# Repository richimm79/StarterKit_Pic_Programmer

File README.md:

# StarterKit_Pic_Programmer
PIC Microcontroller programmer using the StartKit

Please refer to the PIC In-Circuit programming document to understand the meaning of the following content.

This project is not intended to be a professional tool.
There are many programmers on the market and is senseless to create another one.
Use this as a didactic project to understand how the In-Circuit programming works.

This project is a full In-Circuit PIC10 programmer using the StartKit as cpu for logic signal generation.
You need the Adapter circuit to connect the StarteKit to the PIC10 cpu.
This adapter will work in two different ways.
- the socket can be use to insert the PIC device that needs programming. This is clearly a "non In-Circuit" option.
- in the socket can be inserted a plug that connect to the target board. This is the In-Circuit option.
I'm planning to create a 3D printer plug for rapid attach on the target board.
This plug will get the signals from the socket.

You may create your own branch.
You may create your own fork but following the license.
Up to now there is no restriction in wath can be changed.
I just ask to not introduce modern programming paradigmas.
Keep code simple so that anyon can read and understand.

Create a pull-request if you wish to merge it into main.

See wiki page for detailed explanation.
	https://github.com/richimm79/StarterKit_Pic_Programmer/wiki

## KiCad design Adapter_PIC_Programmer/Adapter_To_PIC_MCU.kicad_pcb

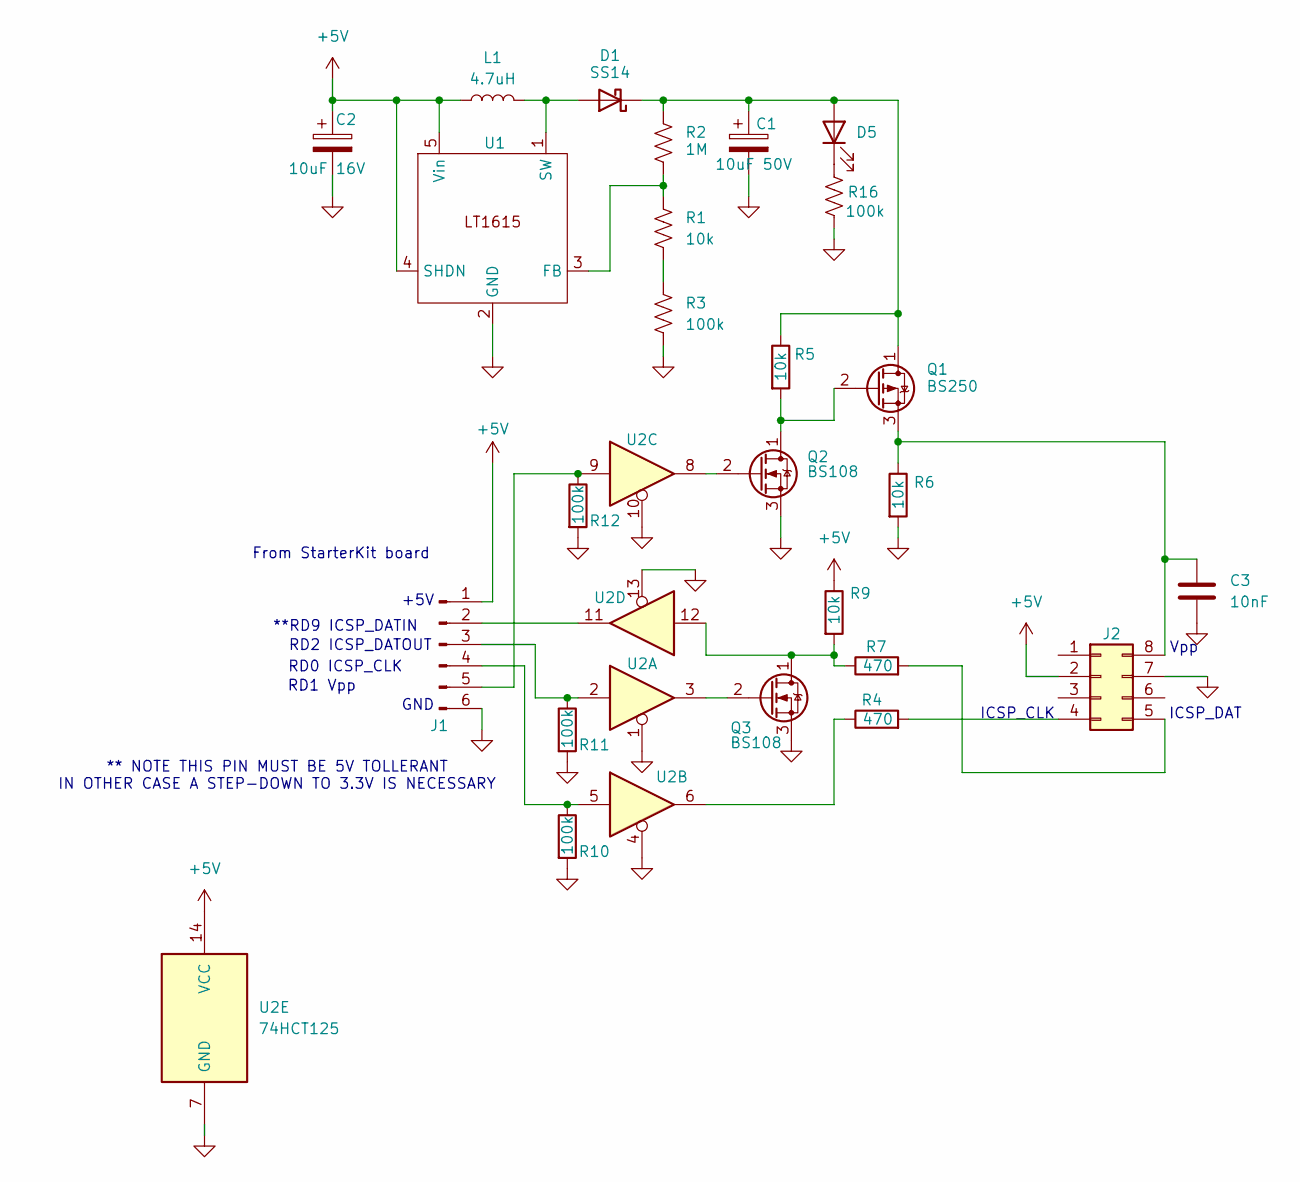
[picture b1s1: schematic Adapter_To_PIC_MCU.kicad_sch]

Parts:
C1: 10uF 50V; CP_Elec_6.3x7.7
C2: 10uF 16V; CP_Elec_5x5.4
C3: 10nF; C_0805_2012Metric_Pad1.18x1.45mm_HandSolder
D1: SS14; D_SMA_Handsoldering
D5: LED; LED_0603_1608Metric
J1: Conn_01x06_Pin; PinSocket_1x06_P2.54mm_SMD
J2: Conn_02x04_Counter_Clockwise; Socket DIL-8 wide pins SMD
L1: 4.7uH; L_Bourns-SRU8028_8.0x8.0mm
Q1: BS250; TO-92L_Inline_Wide SMD_facedown
Q2, Q3: BS108; TO-92L_Inline_Wide SMD_faceup
R1, R5, R6, R9: 10k; R_0805_2012Metric_Pad1.20x1.40mm_HandSolder
R2: 1M; R_0805_2012Metric_Pad1.20x1.40mm_HandSolder
R3, R10, R11, R12, R16: 100k; R_0805_2012Metric_Pad1.20x1.40mm_HandSolder
R4, R7: 470; R_0805_2012Metric_Pad1.20x1.40mm_HandSolder
U1: LT1615; SOT-23-5
U2: 74HCT125; SOIC-14_3.9x8.7mm_P1.27mm

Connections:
+5V: C2.1, J1.1, J2.2, L1.1, R9.1, U1.4 (SHDN), U1.5 (Vin), U2.14 (VCC)
GND: C1.2, C2.2, C3.2, J1.6, J2.7, Q2.3 (S), Q3.3 (S), R3.2, R6.2, R10.2, R11.2, R12.2, R16.2, U1.2 (GND), U2.1, U2.4, U2.7 (GND), U2.10, U2.13
unnamed: D1.2 (A), L1.2, U1.1 (SW)
unnamed: C1.1, D1.1 (K), D5.2 (A), Q1.1 (D), R2.1, R5.1
unnamed: D5.1 (K), R16.1
unnamed: J1.2, U2.11
unnamed: J1.3, R11.1, U2.2
unnamed: J1.4, R10.1, U2.5
unnamed: J1.5, R12.1, U2.9
unnamed: J2.4, R4.2
unnamed: J2.5, R7.2
unnamed: C3.1, J2.8, Q1.3 (S), R6.1
unnamed: Q1.2 (G), Q2.1 (D), R5.2
unnamed: Q2.2 (G), U2.8
unnamed: Q3.1 (D), R7.1, R9.2, U2.12
unnamed: Q3.2 (G), U2.3
unnamed: R1.2, R3.1
unnamed: R4.1, U2.6
unnamed: R1.1, R2.2, U1.3 (FB)

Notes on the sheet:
RD2 ICSP_DATOUT
+5V
RD0 ICSP_CLK
RD1 Vpp
From StarterKit board
ICSP_CLK
**RD9 ICSP_DATIN
** NOTE THIS PIN MUST BE 5V TOLLERANT IN OTHER CASE A STEP-DOWN TO 3.3V IS NECESSARY
ICSP_DAT
Vpp
GND

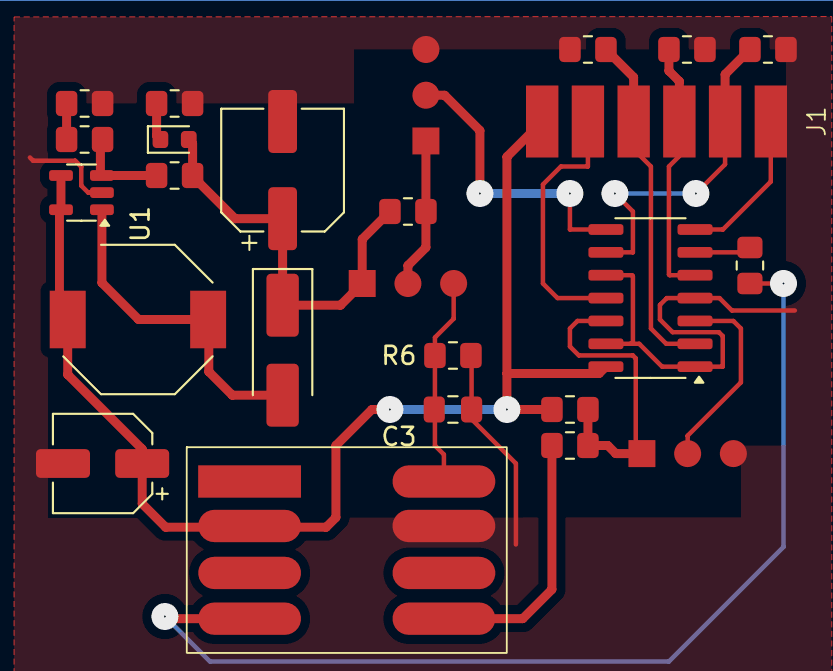
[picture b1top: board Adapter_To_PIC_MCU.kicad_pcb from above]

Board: 2 copper layers, 25 parts (0 on the bottom side), 19 nets.

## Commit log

2025-03-21 First Version
2025-03-23 Readme
